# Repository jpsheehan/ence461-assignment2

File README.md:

# ence461_assignment2
2020 ENCE461 Assignment 2

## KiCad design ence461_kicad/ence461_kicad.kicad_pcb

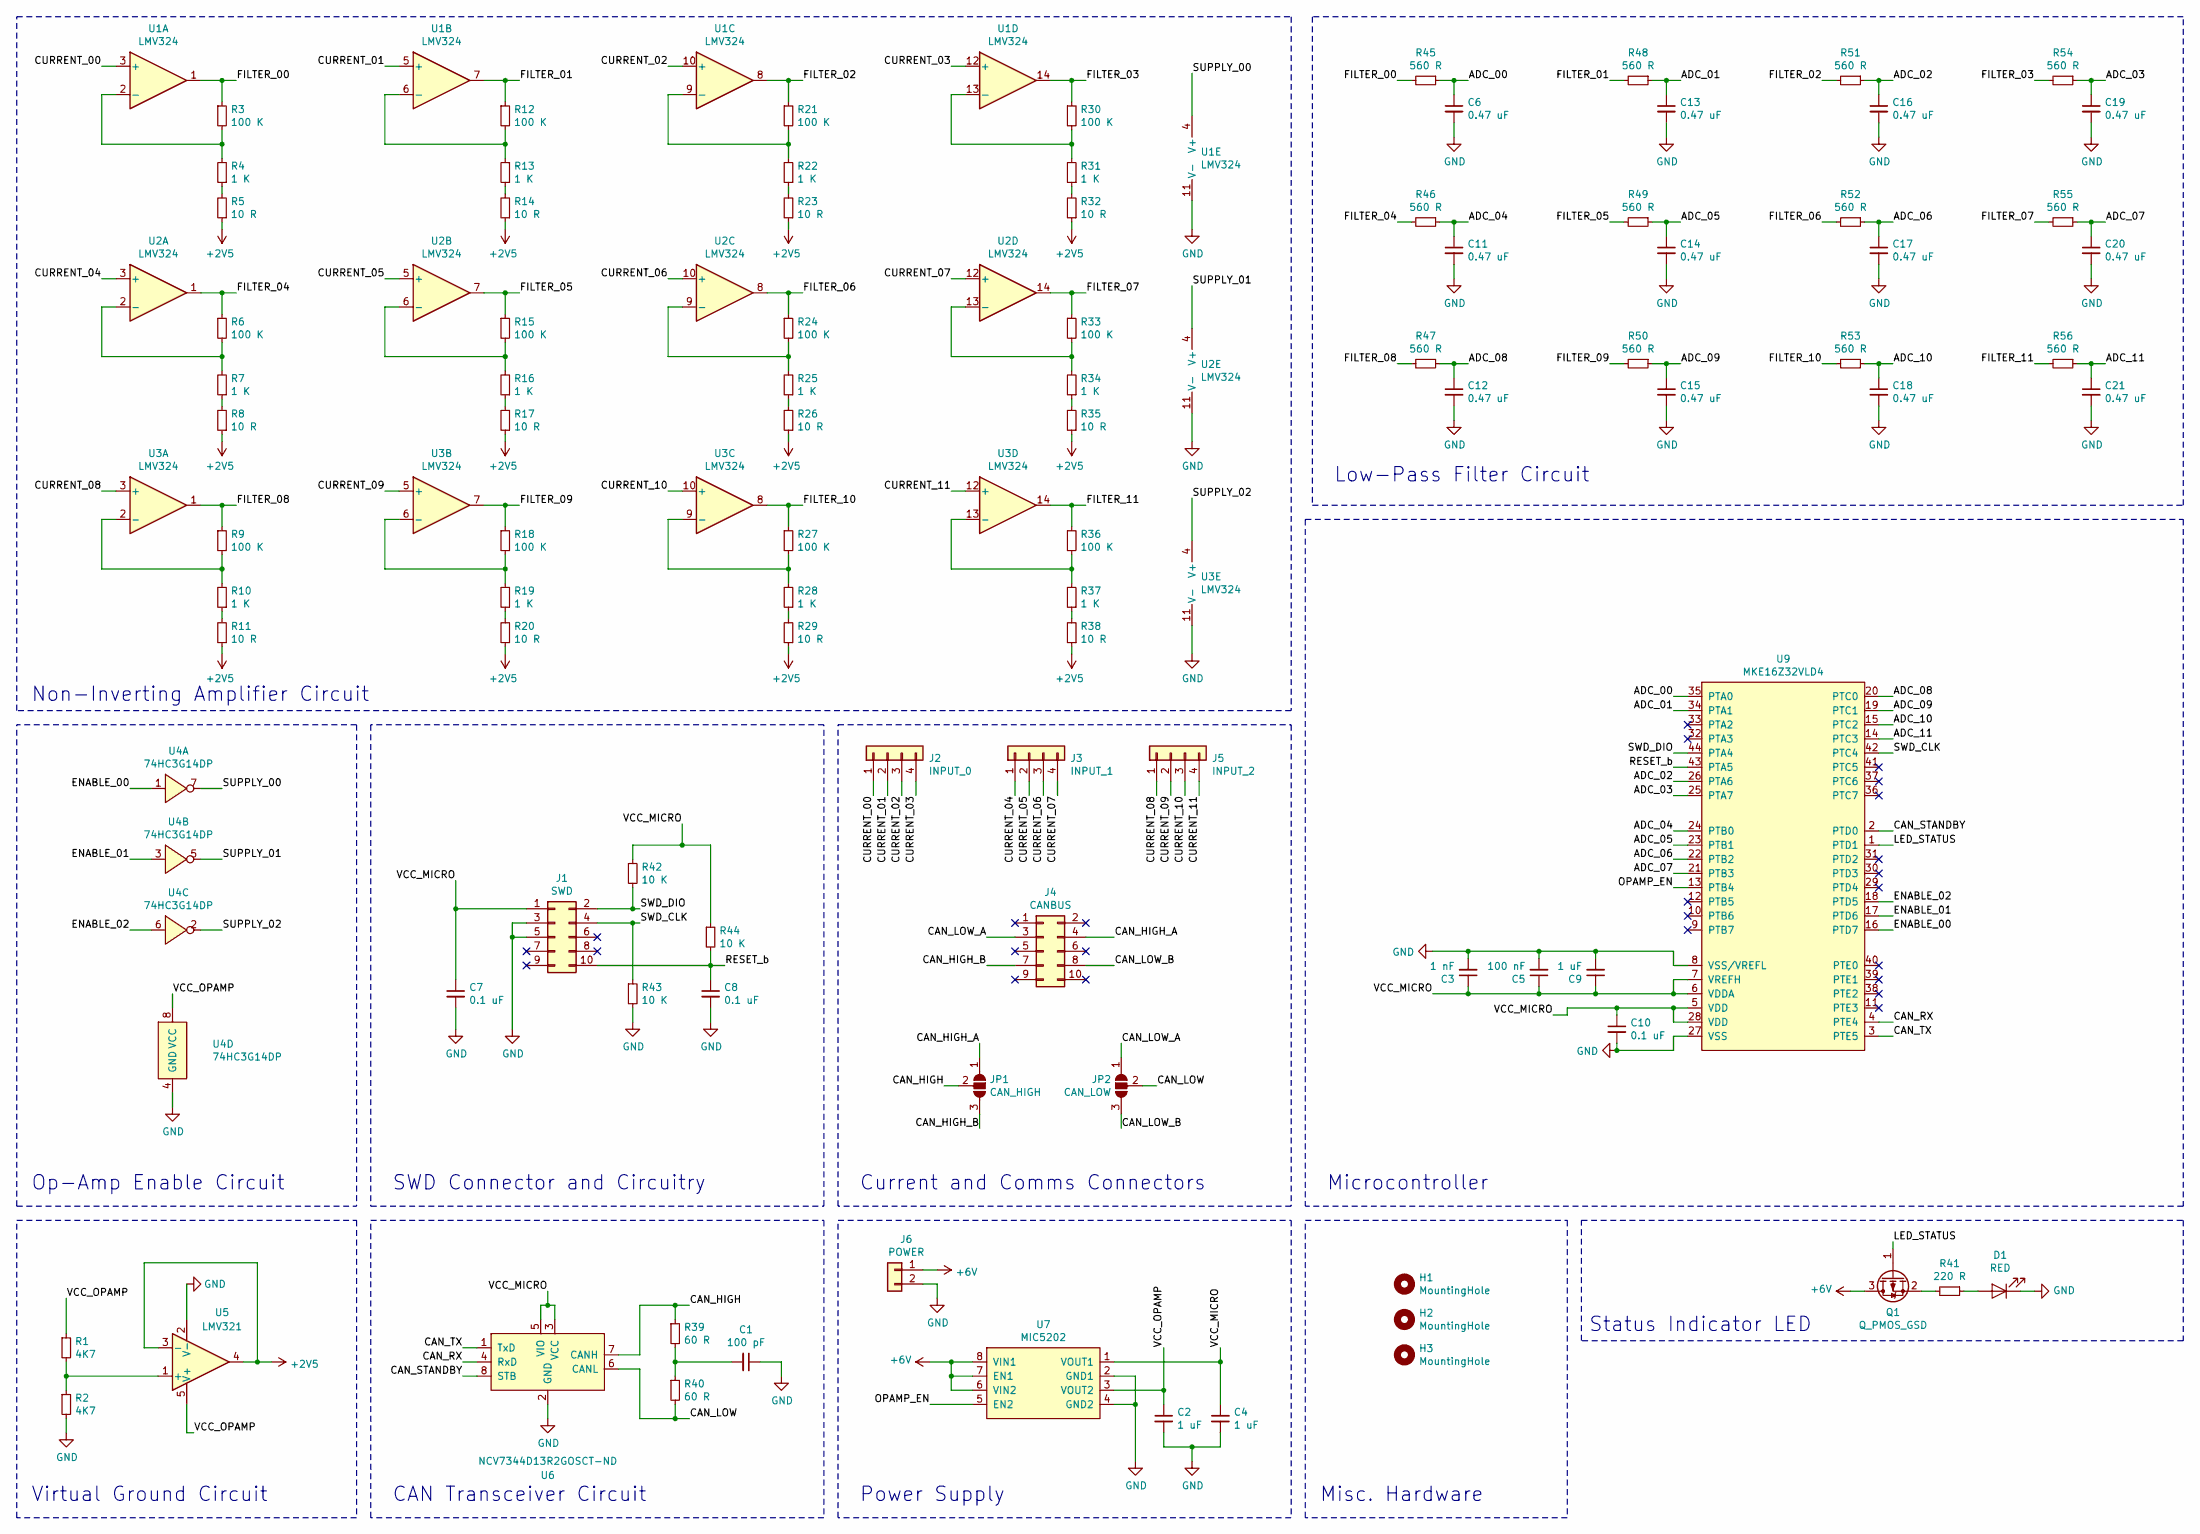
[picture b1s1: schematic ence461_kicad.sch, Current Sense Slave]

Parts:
C1: 100 pF; C_0603_1608Metric
C2, C4, C9: 1 uF; C_0603_1608Metric
C3: 1 nF; C_0603_1608Metric
C5: 100 nF; C_0603_1608Metric
C6, C11, C12, C13, C14, C15, C16, C17, C18, C19, C20, C21: 0.47 uF; C_0402_1005Metric
C7, C8, C10: 0.1 uF; C_0603_1608Metric
D1: RED; LED_PLCC-2
H1, H2, H3: MountingHole; MountingHole_3mm
J1: SWD; PinHeader_2x05_P1.27mm_Vertical
J2: INPUT_0; PinSocket_1x04_P1.27mm_Vertical
J3: INPUT_1; PinSocket_1x04_P1.27mm_Vertical
J4: CANBUS; PinHeader_2x05_P1.27mm_Vertical
J5: INPUT_2; PinSocket_1x04_P1.27mm_Vertical
J6: POWER; TB002-500
JP1: CAN_HIGH; SolderJumper-3_P1.3mm_Open_Pad1.0x1.5mm
JP2: CAN_LOW; SolderJumper-3_P1.3mm_Open_Pad1.0x1.5mm
Q1: Q_PMOS_GSD; SOT-723
R1, R2: 4K7; R_0603_1608Metric
R3, R6, R9, R12, R15, R18, R21, R24, R27, R30, R33, R36: 100 K; R_0603_1608Metric
R4, R7, R10, R13, R16, R19, R22, R25, R28, R31, R34, R37: 1 K; R_0603_1608Metric
R5, R8, R11, R14, R17, R20, R23, R26, R29, R32, R35, R38: 10 R; R_0603_1608Metric
R39, R40: 60 R; R_0603_1608Metric
R41: 220 R; R_0603_1608Metric
R42, R43, R44: 10 K; R_0603_1608Metric
R45, R46, R47, R48, R49, R50, R51, R52, R53, R54, R55, R56: 560 R; R_0402_1005Metric
U1, U2, U3: LMV324; TSSOP-14_4.4x5mm_P0.65mm
U4: 74HC3G14DP; VSSOP-8_2.3x2mm_P0.5mm
U5: LMV321; SOT-23-5
U6: NCV7344D13R2GOSCT-ND; SOIC-8_3.9x4.9mm_P1.27mm
U7: MIC5202; SOIC-8_3.9x4.9mm_P1.27mm
U9: MKE16Z32VLD4; LQFP-44_10x10mm_P0.8mm

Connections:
+2V5: R5.1, R8.1, R11.1, R14.1, R17.1, R20.1, R23.1, R26.1, R29.1, R32.1, R35.1, R38.1, U5.3 (-), U5.4
+6V: J6.1, Q1.3 (D), U7.6 (VIN2), U7.7 (EN1), U7.8 (VIN1)
/ADC_00: C6.1, R45.1, U9.35 (PTA0)
/ADC_01: C13.1, R48.1, U9.34 (PTA1)
/ADC_02: C16.1, R51.1, U9.26 (PTA6)
/ADC_03: C19.1, R54.1, U9.25 (PTA7)
/ADC_04: C11.1, R46.1, U9.24 (PTB0)
/ADC_05: C14.1, R49.1, U9.23 (PTB1)
/ADC_06: C17.1, R52.1, U9.22 (PTB2)
/ADC_07: C20.1, R55.1, U9.21 (PTB3)
/ADC_08: C12.1, R47.1, U9.20 (PTC0)
/ADC_09: C15.1, R50.1, U9.19 (PTC1)
/ADC_10: C18.1, R53.1, U9.15 (PTC2)
/ADC_11: C21.1, R56.1, U9.14 (PTC3)
/CAN_HIGH: JP1.2 (C), R39.1, U6.7 (CANH)
/CAN_HIGH_A: J4.4, JP1.1 (A)
/CAN_HIGH_B: J4.7, JP1.3 (B)
/CAN_LOW: JP2.2 (C), R40.2, U6.6 (CANL)
/CAN_LOW_A: J4.3, JP2.1 (A)
/CAN_LOW_B: J4.8, JP2.3 (B)
/CAN_RX: U6.4 (RxD), U9.4 (PTE4)
/CAN_STANDBY: U6.8 (STB), U9.2 (PTD0)
/CAN_TX: U6.1 (TxD), U9.3 (PTE5)
/CURRENT_00: J2.1, U1.3 (+)
/CURRENT_01: J2.2, U1.5 (+)
/CURRENT_02: J2.3, U1.10 (+)
/CURRENT_03: J2.4, U1.12 (+)
/CURRENT_04: J3.1, U2.3 (+)
/CURRENT_05: J3.2, U2.5 (+)
/CURRENT_06: J3.3, U2.10 (+)
/CURRENT_07: J3.4, U2.12 (+)
/CURRENT_08: J5.1, U3.3 (+)
/CURRENT_09: J5.2, U3.5 (+)
/CURRENT_10: J5.3, U3.10 (+)
/CURRENT_11: J5.4, U3.12 (+)
/ENABLE_00: U4.1, U9.16 (PTD7)
/ENABLE_01: U4.3, U9.17 (PTD6)
/ENABLE_02: U4.6, U9.18 (PTD5)
/FILTER_00: R3.1, R45.2, U1.1
/FILTER_01: R12.1, R48.2, U1.7
/FILTER_02: R21.1, R51.2, U1.8
/FILTER_03: R30.1, R54.2, U1.14
/FILTER_04: R6.1, R46.2, U2.1
/FILTER_05: R15.1, R49.2, U2.7
/FILTER_06: R24.1, R52.2, U2.8
/FILTER_07: R33.1, R55.2, U2.14
/FILTER_08: R9.1, R47.2, U3.1
/FILTER_09: R18.1, R50.2, U3.7
/FILTER_10: R27.1, R53.2, U3.8
/FILTER_11: R36.1, R56.2, U3.14
/LED_STATUS: Q1.1 (G), U9.1 (PTD1)
/OPAMP_EN: U7.5 (EN2), U9.13 (PTB4)
/RESET_b: C8.1, J1.10, R44.2, U9.43 (PTA5)
/SUPPLY_00: U1.4 (V+), U4.7
/SUPPLY_01: U2.4 (V+), U4.5
/SUPPLY_02: U3.4 (V+), U4.2
/SWD_CLK: J1.4, R43.1, U9.42 (PTC4)
/SWD_DIO: J1.2, R42.2, U9.44 (PTA4)
/VCC_MICRO: C3.1, C4.1, C5.1, C7.1, C9.1, C10.1, J1.1, R42.1, R44.1, U6.3 (VCC), U6.5 (VIO), U7.1 (VOUT1), U9.5 (VDD), U9.6 (VDDA), U9.7 (VREFH), U9.28 (VDD)
/VCC_OPAMP: C2.1, R1.1, U4.8 (VCC), U5.5 (V+), U7.3 (VOUT2)
GND: C1.1, C2.2, C3.2, C4.2, C5.2, C6.2, C7.2, C8.2, C9.2, C10.2, C11.2, C12.2, C13.2, C14.2, C15.2, C16.2, C17.2, C18.2, C19.2, C20.2, C21.2, D1.1 (K), J1.3, J1.5, J6.2, R2.2, R43.2, U1.11 (V-), U2.11 (V-), U3.11 (V-), U4.4 (GND), U5.2 (V-), U6.2 (GND), U7.2 (GND1), U7.4 (GND2), U9.8 (VSS/VREFL), U9.27 (VSS)
unnamed: C1.2, R39.2, R40.1
unnamed: D1.2 (A), R41.1
unnamed: Q1.2 (S), R41.2
unnamed: R1.2, R2.1, U5.1 (+)
unnamed: R3.2, R4.2, U1.2 (-)
unnamed: R4.1, R5.2
unnamed: R6.2, R7.2, U2.2 (-)
unnamed: R7.1, R8.2
unnamed: R10.1, R11.2
unnamed: R9.2, R10.2, U3.2 (-)
unnamed: R12.2, R13.2, U1.6 (-)
unnamed: R13.1, R14.2
unnamed: R15.2, R16.2, U2.6 (-)
unnamed: R16.1, R17.2
unnamed: R18.2, R19.2, U3.6 (-)
unnamed: R19.1, R20.2
unnamed: R21.2, R22.2, U1.9 (-)
unnamed: R22.1, R23.2
unnamed: R24.2, R25.2, U2.9 (-)
unnamed: R25.1, R26.2
unnamed: R27.2, R28.2, U3.9 (-)
unnamed: R28.1, R29.2
unnamed: R30.2, R31.2, U1.13 (-)
unnamed: R31.1, R32.2
unnamed: R33.2, R34.2, U2.13 (-)
unnamed: R34.1, R35.2
unnamed: R36.2, R37.2, U3.13 (-)
unnamed: R37.1, R38.2

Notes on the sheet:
Op-Amp Enable Circuit
Non-Inverting Amplifier Circuit
Virtual Ground Circuit
CAN Transceiver Circuit
Power Supply
SWD Connector and Circuitry
Current and Comms Connectors
Status Indicator LED
Low-Pass Filter Circuit
Misc. Hardware
Microcontroller

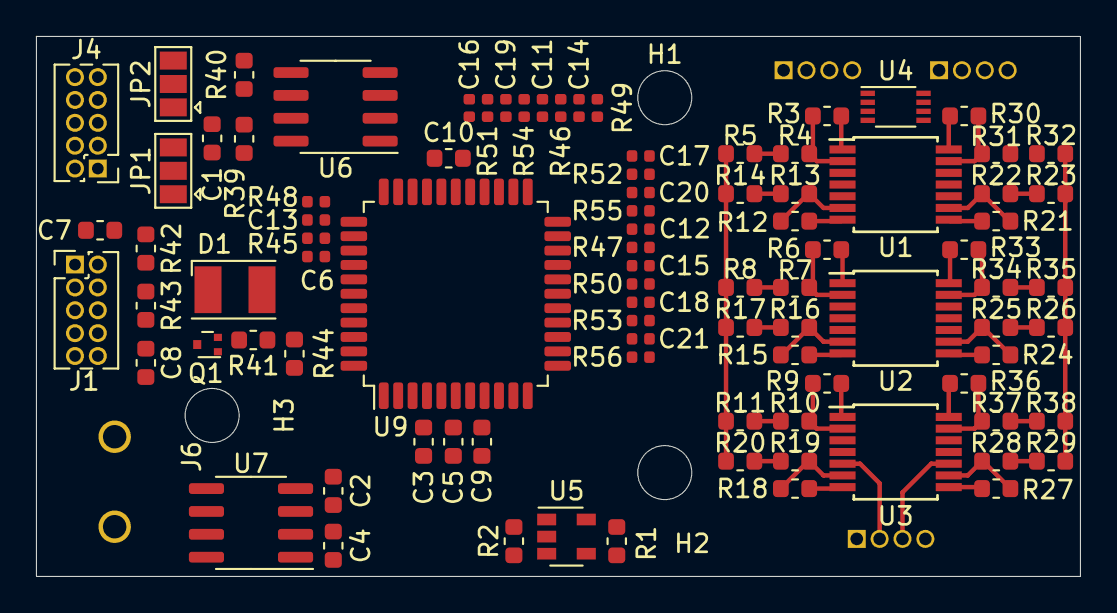
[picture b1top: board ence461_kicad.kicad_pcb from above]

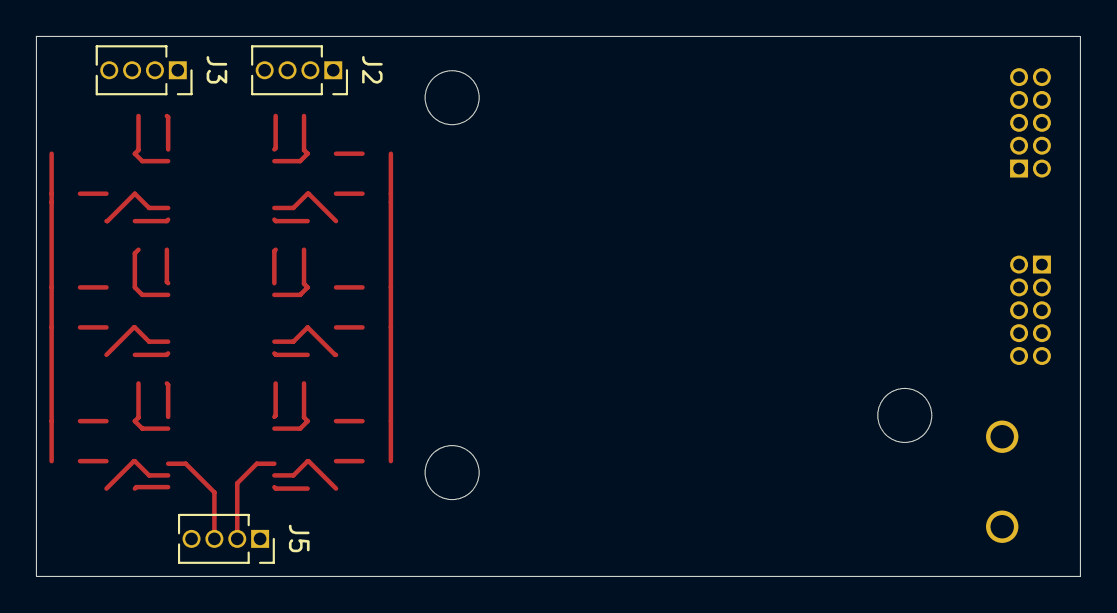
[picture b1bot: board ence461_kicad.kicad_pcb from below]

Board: 2 copper layers, 58.0 x 30.0 mm, 98 parts (3 on the bottom side), 89 nets.

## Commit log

2020-05-20 Added skeleton report.
2020-05-20 Added v2 of specification.
2020-05-21 Added datasheets directory.
2020-05-21 Linear 5V regulator datasheets
2020-05-21 Added opamp datasheet
2020-05-21 Started a parts list
2020-05-21 PSU option 2 - combined micro/ADC
2020-05-21 Added opamp info.
2020-05-21 Added VIM swap files to gitignore.
2020-05-21 Added empty kicad project.
2020-05-21 Changed opamp part.
2020-05-21 Regulator thermal calcs & pricing
2020-05-21 Why doesn't Parts track
2020-05-22 Added non-inverting op-amp circuits.
2020-05-22 Wrote a bit about the op-amp design.
2020-05-22 Reinstate Parts research notes
2020-05-22 Added more words about op-amps
2020-05-22 Add text on thermal stuff and OpAmp design
2020-05-22 Added circuit images.
2020-05-22 Split off opamp and example into own files.
2020-05-22 Split all sections. Added build.bat.
2020-05-22 Added op amps to schematic. Specced an opamp for virtual gnd.
2020-05-22 Buss comms
2020-05-22 Fixed up the opamp images.
2020-05-22 Added CAN transceiver datasheet
2020-05-22 Update buss topology
2020-05-22 Added hex inverter stuff
2020-05-22 Respecced the inverter
2020-05-22 Added CAN transceiver symbol to schematic.
2020-05-22 Update 3V# regulator
2020-05-22 Added TPS717 symbol to schematic.
2020-05-22 Added TPS714 supply.
2020-05-22 Added stubs for external connectors.
2020-05-23 Added some stubs for micro gpio
2020-05-23 3V3 PSU update
2020-05-23 Update comms selection
2020-05-23 3V3 thermal calc, explain design preference
2020-05-23 Added an LED, not 100% sure tho
2020-05-23 Added LED status indicator.
2020-05-23 Added LED to schematic.
2020-05-23 Added more words to the op-amp report.
2020-05-23 Added a reference to virtual ground op-amp
2020-05-23 Added micro info.
2020-05-23 Update comms & regulators
2020-05-23 3V3 thermal calcs
2020-05-23 Changed micro :(
2020-05-23 New 5V PSU design, remove old PSU pdf's
2020-05-23 Starting cables, connectors, update buss sheet
2020-05-23 Removed old SAM micro datasheet
2020-05-23 Added micro to schematic. Laid out.
2020-05-23 Forgot to save.
2020-05-23 Added datasheet and refman for micro.
2020-05-23 Added symbol for new power supply to schematic.
2020-05-24 Changed amplifier gain to 141
2020-05-24 Added RC filtering.
2020-05-24 Spec'd data cable and connectors
2020-05-24 Data buss interconnect part numbers
2020-05-24 Data buss datasheets
2020-05-24 Almost there!
2020-05-24 Added datasheet for power connector.
2020-05-24 Finished layout.
2020-05-24 Added a model for the power connector.
2020-05-24 Power cable & parts
2020-05-24 Removed some temp files.
2020-05-24 Added power connector.
2020-05-24 notes on data cable
2020-05-24 Introduction written
2020-05-24 Working on conditioning
2020-05-24 Power supply section started
2020-05-25 Finish PSU section and update buss options
2020-05-25 Added more words to conditioning
2020-05-25 Changed gain stage to equal 100
2020-05-25 Added schematics for diagrams. Fixed virtual ground mistake.
2020-05-25 Added more diagrams.
2020-05-25 Added conditioning block diagram.
2020-05-25 PSU section temp notes
2020-05-25 Added opamp calcs to appendix.
2020-05-25 Added more calcs to appendix
2020-05-25 Added microcontroller section.
2020-05-25 started comms section
2020-05-25 Update appendix pull, start thermal
2020-05-25 Added PCB layout section.
2020-05-25 Fixed compile errors.
2020-05-25 Cleaned up comms section.
2020-05-25 Thermal stuff
2020-05-25 Added schematic to appendix.
2020-05-25 Added bom
2020-05-25 Update schematic title
2020-05-25 General tidying up
2020-05-25 More details added.
2020-05-25 More formatting
2020-05-25 BOM in pdf
2020-05-25 Allowed pdfs in includes folder
2020-05-25 now the bom in pdf
2020-05-25 Words on thermal and power supply.
2020-05-25 Added stuff to appendix.
2020-05-25 Added conclusion
2020-05-25 Fix current consumption words
2020-05-25 Gussy's proof read
2020-05-25 Fixed a thing in micro.
2020-05-25 SPelling
2020-05-25 Specced master micro
2020-05-25 comms
